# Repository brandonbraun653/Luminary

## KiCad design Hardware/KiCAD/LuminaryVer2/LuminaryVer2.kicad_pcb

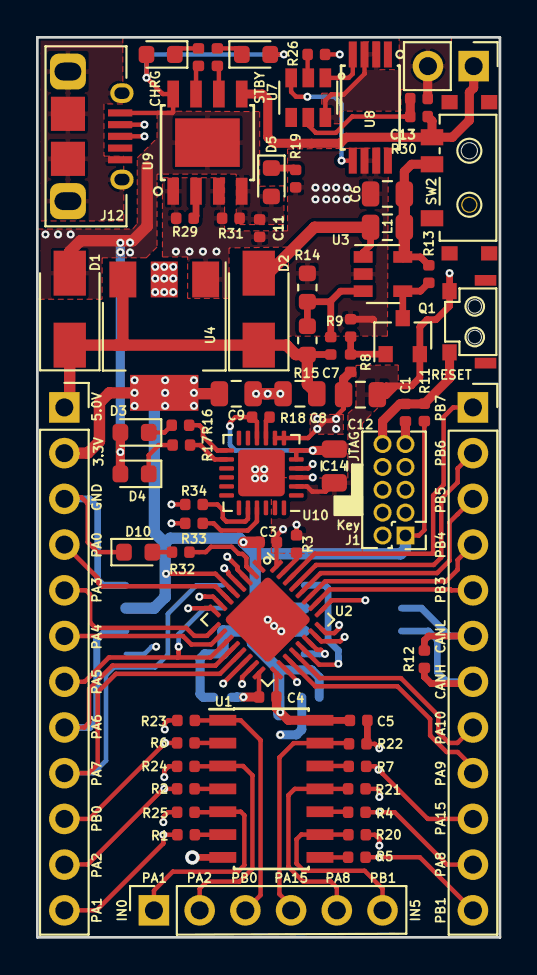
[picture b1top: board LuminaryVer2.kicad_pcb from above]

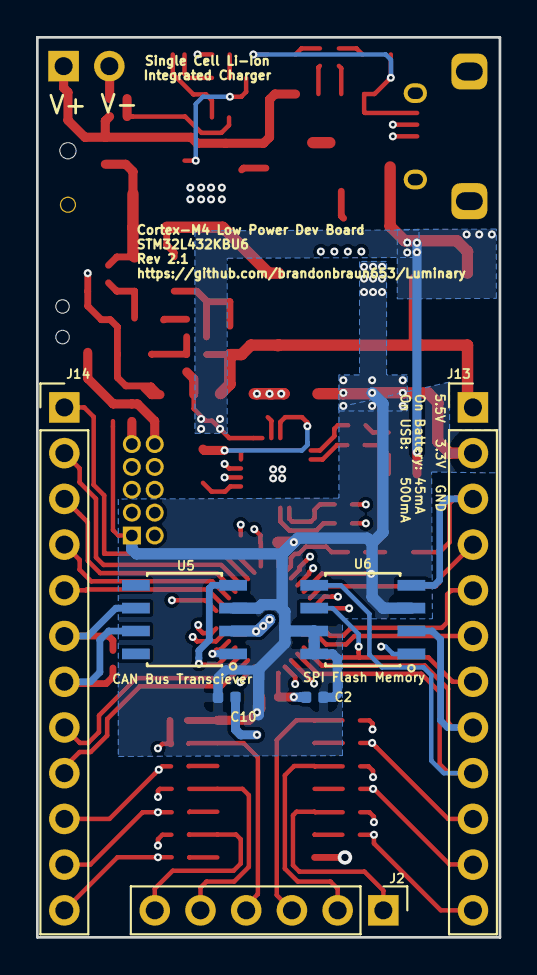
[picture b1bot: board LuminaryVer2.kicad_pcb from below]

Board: 4 copper layers, 25.7 x 50.0 mm, 75 parts (7 on the bottom side), 73 nets.

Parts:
C1, C2, C3, C4, C5, C10, C11, C13: 100nF; C_0402_1005Metric
C6, C8: 10uF; C_0805_2012Metric
C7: 3.3pF; C_0402_1005Metric
C9, C12, C14: 1uF; C_0805_2012Metric
D1, D2: SS14; D_SMA
D3, D4, D5, D9: BLED; D_0603_1608Metric
D8: RLED; D_0603_1608Metric
D10: GLED; D_0603_1608Metric
J1: JTAG; PinHeader_2x05_P1.27mm_Vertical
J2: GPIOInput; PinHeader_1x06_P2.54mm_Vertical
J10: ExtBattPwr; PinHeader_1x02_P2.54mm_Vertical
J12: USB_B_Micro; Amphenol-MicroB
J13: CN1; PinHeader_1x12_P2.54mm_Vertical
J14: CN2; PinHeader_1x12_P2.54mm_Vertical
L1: 3.3uH; L_0805_2012Metric
Q1: MMBT3904; SOT-23
R1, R2, R4, R5, R6, R7, R20, R21, R22, R23, R24, R25, R31: 47k; R_0402_1005Metric
R3, R9, R11, R13, R29, R32: 10k; R_0402_1005Metric
R8: 100; R_0402_1005Metric
R12, R30: 120; R_0402_1005Metric
R14: 200k; R_0603_1608Metric
R15: 620k; R_0603_1608Metric
R16, R17, R18, R19, R26, R27, R28, R33, R34: 1k; R_0402_1005Metric
SW1: SW_Push; LCSC_C255808_HYP_2x4x3.5mm_RightAngle
SW2: SW_BATT_DISCONNECT; LCSC_C136659_HRO_SPDT_6.7x2.6mm_ToggleSwitch
U1: 74HC14; SOIC-14_3.9x8.7mm_P1.27mm
U2: STM32L432KBUx; QFN-32-1EP_5x5mm_P0.5mm_EP3.45x3.45mm
U3: TPS61040; SOT-23-5
U4: AMS1117-3.3; SOT-223-3_TabPin2
U5: SN65HVD232; SOIC-8_3.9x4.9mm_P1.27mm
U6: AT25SF081-SSHD-X; SOIC-8_3.9x4.9mm_P1.27mm
U7: DW01+G; SOT-23-6
U8: FS8205A; TSSOP-8_4.4x3mm_P0.65mm
U9: TP4056; TP4056_SOP-8-PP
U10: CP2104; QFN-24-1EP_4x4mm_P0.5mm_EP2.6x2.6mm

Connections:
+3V3: C2.2, C3.1, C4.2, C5.2, C9.1, C10.2, J1.1, J13.2, R11.2, U1.14, U2.1, U2.5, U2.17, U4.2, U5.3, U6.3, U6.7, U6.8
+5V: C7.1, C8.2, D1.1, D2.1, J13.1, R15.1, U4.3
/Input Connectors/Batt_V+: J10.1, R30.1, SW2.1, U9.5
/Input Connectors/Batt_V-: C13.2, J10.2, U7.6, U8.2, U8.3
/Input Connectors/D+: J12.3, U10.3
/Input Connectors/D-: J12.2, U10.4
/Input Connectors/GPIO_INPUT_0: R1.1, U1.6
/Input Connectors/GPIO_INPUT_1: R2.2, U1.4
/Input Connectors/GPIO_INPUT_2: R6.2, U1.2
/Input Connectors/GPIO_INPUT_3: R7.2, U1.12
/Input Connectors/GPIO_INPUT_4: R4.2, U1.10
/Input Connectors/GPIO_INPUT_5: R5.2, U1.8
/Input Connectors/nRESET: C1.2, J1.10, R11.1, SW1.2, U2.4
/Output Connectors/CAN_1_HI: J14.7, R12.1, U5.7
/Output Connectors/CAN_1_LO: J14.6, R12.2, U5.6
/Output Connectors/I2C_1_SCL: J14.2, U2.29
/Output Connectors/I2C_1_SDA: J14.1, U2.30
/Output Connectors/RS232_1_RX: J14.8, R33.2, U2.20
/Output Connectors/RS232_1_TX: J14.9, R34.2, U2.19
/Output Connectors/SPI_1_MISO: J13.8, U2.12, U6.2
/Output Connectors/SPI_1_MOSI: J13.9, U2.13, U6.5
/Output Connectors/SPI_1_SCK: J13.7, U2.11, U6.6
/Output Connectors/SPI_2_MISO: J14.4, U2.27
/Output Connectors/SPI_2_MOSI: J14.3, U2.28
/Output Connectors/SPI_2_SCK: J14.5, U2.26
/Power Supply/Ext_In+: C11.1, C12.2, D1.2, D3.2, D4.2, D5.2, D8.2, D9.2, J12.1, R8.2, R31.2, U9.4, U9.8, U9.9, U10.7, U10.8
/Processor/ADC_0: J13.4, U2.6
/Processor/ADC_1: J13.5, U2.9
/Processor/ADC_2: J13.6, U2.10
/Processor/CAN_1_RX: U2.21, U5.4
/Processor/CAN_1_TX: U2.22, U5.1
/Processor/GPIO_0: J13.12, R1.2, U2.7
/Processor/GPIO_1: J13.11, R2.1, U2.8
/Processor/GPIO_2: J13.10, R6.1, U2.14
/Processor/GPIO_3: J14.10, R7.1, U2.25
/Processor/GPIO_4: J14.11, R4.1, U2.18
/Processor/GPIO_5: J14.12, R5.1, U2.15
/Processor/SWCLK: J1.4, U2.24
/Processor/SWDIO: J1.2, U2.23
FlashCS: U2.3, U6.1
GND: C1.1, C2.1, C3.2, C4.1, C5.1, C6.1, C8.1, C9.2, C10.1, C11.2, C12.1, C14.2, D10.1, J1.3, J1.5, J1.9, J12.5, J12.6, J13.3, Q1.2, R3.2, R9.1, R14.1, R19.1, R20.1, R21.1, R22.1, R23.1, R24.1, R25.1, R26.2, R29.2, R31.1, SW1.1, U1.7, U2.16, U2.32, U2.33, U3.2, U4.1, U5.2, U6.4, U8.6, U8.7, U9.1, U9.3, U10.2, U10.25
unnamed: C6.2, L1.1, R13.2, SW2.2, U3.5
unnamed: C7.2, R14.2, R15.2, U3.3
unnamed: C13.1, R30.2, U7.5
unnamed: C14.1, R18.2, U10.5, U10.6, U10.10
unnamed: D2.2, L1.2, U3.1
unnamed: D3.1, R16.2
unnamed: D4.1, R17.2
unnamed: D5.1, R19.2
unnamed: D8.1, R27.2
unnamed: D9.1, R28.2
unnamed: D10.2, R32.1
unnamed: J2.1, R25.2, U1.5
unnamed: J2.2, R24.2, U1.3
unnamed: J2.3, R23.2, U1.1
unnamed: J2.4, R22.2, U1.13
unnamed: J2.5, R21.2, U1.11
unnamed: J2.6, R20.2, U1.9
unnamed: Q1.1, R8.1, R9.2
unnamed: Q1.3, R13.1, U3.4
unnamed: R3.1, U2.31
unnamed: R16.1, U10.13
unnamed: R17.1, U10.14
unnamed: R18.1, U10.9
unnamed: R26.1, U7.2
unnamed: R27.1, U9.7
unnamed: R28.1, U9.6
unnamed: R29.1, U9.2
unnamed: R33.1, U10.21
unnamed: R34.1, U10.20
unnamed: U7.1, U8.4
unnamed: U7.3, U8.5
StatusLED: R32.2, U2.2

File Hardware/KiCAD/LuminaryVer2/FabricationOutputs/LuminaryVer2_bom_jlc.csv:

"Comment","Designator","Footprint","LCSC Part #"
"100nF","C5,C13,C11,C3,C4,C1,C2,C10","C_0402_1005Metric","C1525"
"10uF","C6,C8","C_0805_2012Metric","C15850"
"3.3pF","C7","C_0402_1005Metric","C1565"
"1uF","C9,C14,C12","C_0805_2012Metric","C28323"
"SS14","D1,D2","D_SMA","C2480"
"RLED","D8","D_0603_1608Metric","C2286"
"BLED","D9,D5,D4,D3","D_0603_1608Metric","C72041"
"GLED","D10","D_0603_1608Metric","C72043"
"3.3uH","L1","L_0805_2012Metric","C51725"
"MMBT3904","Q1","SOT-23","C20526"
"100","R8","R_0402_1005Metric","C25076"
"10k","R9,R29,R13,R3,R11,R32","R_0402_1005Metric","C25744"
"200k","R14","R_0603_1608Metric","C25811"
"620k","R15","R_0603_1608Metric","C23219"
"47k","R25,R23,R21,R22,R24,R20,R31,R1,R2,R6,R7,R4,R5","R_0402_1005Metric","C25792"
"1k","R27,R28,R26,R19,R16,R17,R18,R33,R34","R_0402_1005Metric","C11702"
"120","R30,R12","R_0402_1005Metric","C25079"
"SW_Push","SW1","LCSC_C255808_HYP_2x4x3.5mm_RightAngle","C255808"
"SW_BATT_DISCONNECT","SW2","LCSC_C136659_HRO_SPDT_6.7x2.6mm_ToggleSwitch","C136659"
"74HC14","U1","SOIC-14_3.9x8.7mm_P1.27mm","C5605"
"STM32L432KBUx","U2","QFN-32-1EP_5x5mm_P0.5mm_EP3.45x3.45mm","C94784"
"TPS61040","U3","SOT-23-5","C7722"
"AMS1117-3.3","U4","SOT-223-3_TabPin2","C6186"
"SN65HVD232","U5","SOIC-8_3.9x4.9mm_P1.27mm","C30530"
"AT25SF081-SSHD-X","U6","SOIC-8_3.9x4.9mm_P1.27mm","C169368"
"DW01+G","U7","SOT-23-6","C14213"
"FS8205A","U8","TSSOP-8_4.4x3mm_P0.65mm","C16052"
"TP4056","U9","TP4056_SOP-8-PP","C16581"
"CP2104","U10","QFN-24-1EP_4x4mm_P0.5mm_EP2.6x2.6mm","C47742"

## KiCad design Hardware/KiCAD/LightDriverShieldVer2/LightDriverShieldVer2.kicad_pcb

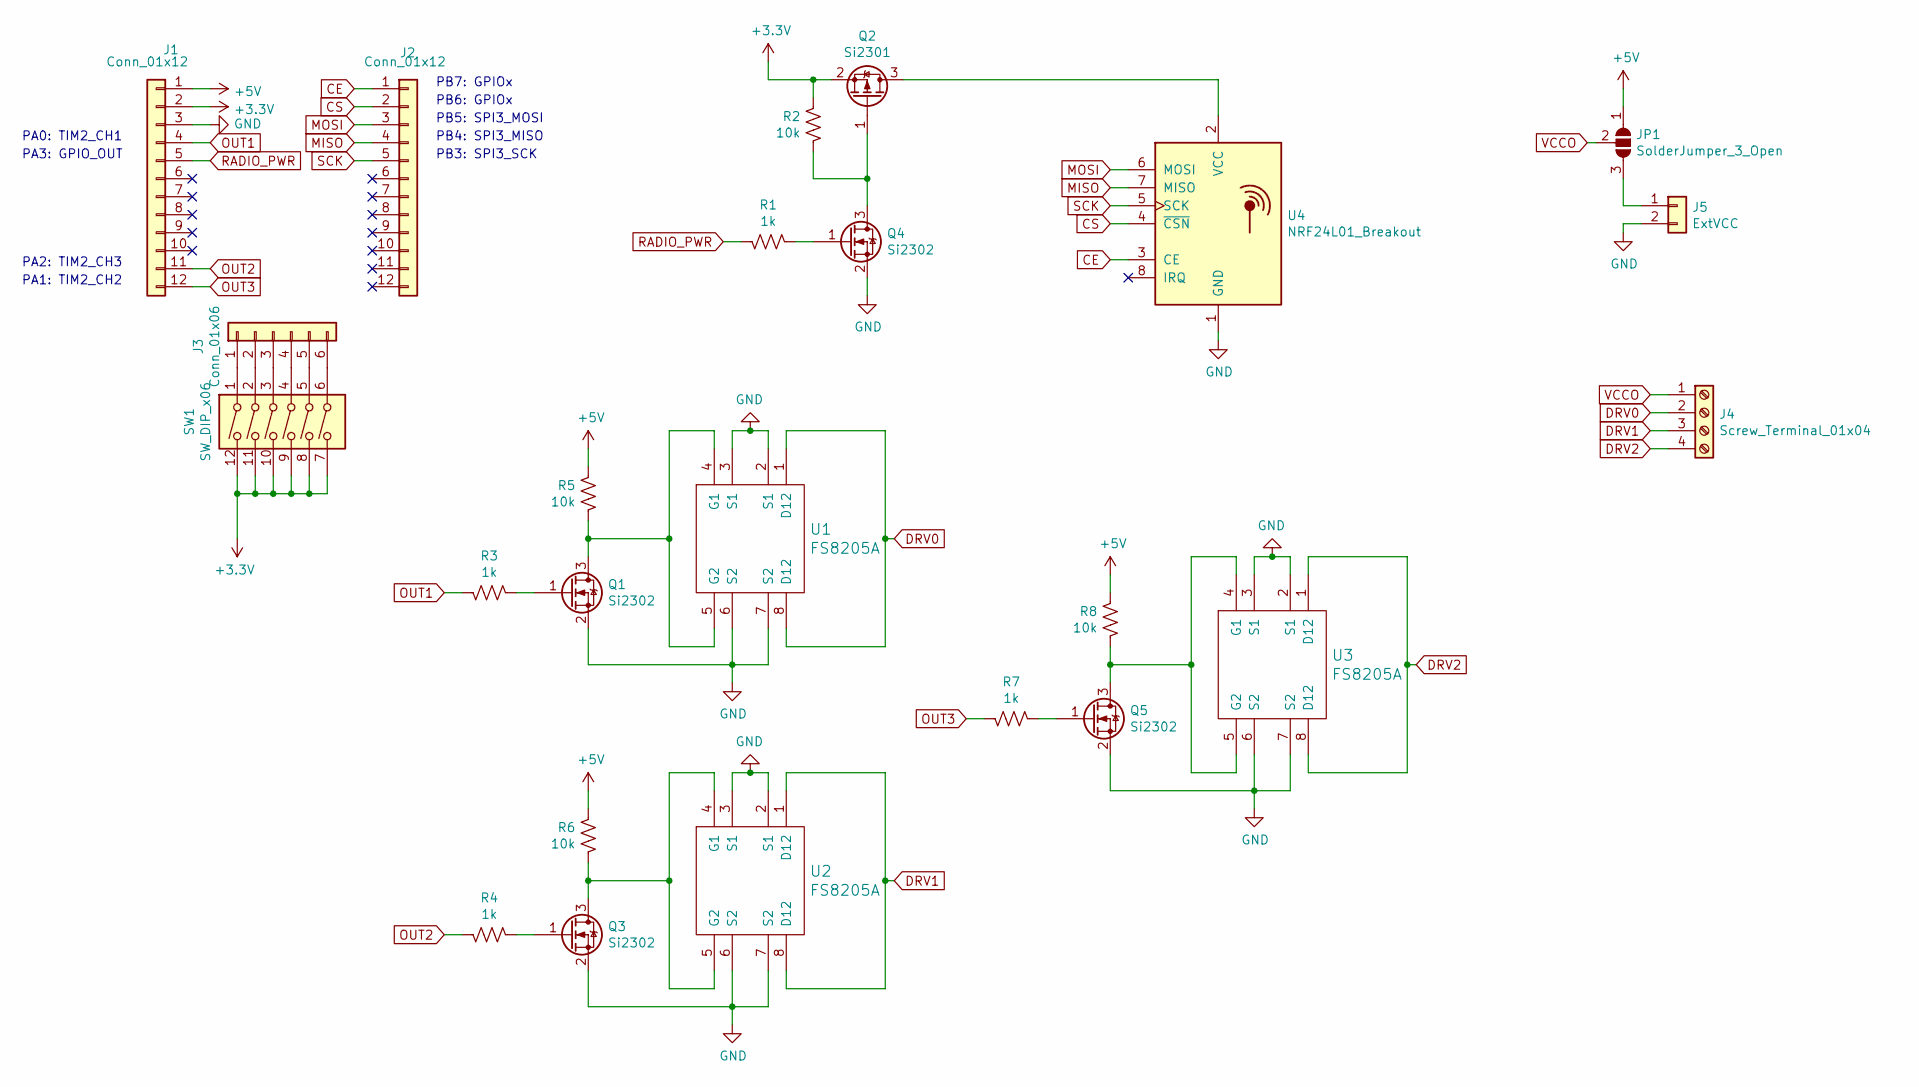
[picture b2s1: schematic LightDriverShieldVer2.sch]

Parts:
J1, J2: Conn_01x12; PinSocket_1x12_P2.54mm_Vertical
J3: Conn_01x06; PinSocket_1x06_P2.54mm_Vertical
J4: Screw_Terminal_01x04; TerminalBlock_TE_282834-4_1x04_P2.54mm_Horizontal
J5: ExtVCC; PinHeader_1x02_P2.54mm_Vertical
JP1: SolderJumper_3_Open; SolderJumper-3_P2.0mm_Open_TrianglePad1.0x1.5mm_NumberLabels
Q1, Q3, Q4, Q5: Si2302; SOT-23; LCSC C181087
Q2: Si2301; SOT-23; LCSC C10487
R1, R3, R4, R7: 1k; R_0402_1005Metric
R2, R5, R6, R8: 10k; R_0402_1005Metric
SW1: SW_DIP_x06; SW_DIP_SPSTx06_Slide_6.7x16.8mm_W7.62mm_P2.54mm_LowProfile
U1, U2, U3: FS8205A; TSSOP-8_4.4x3mm_P0.65mm; LCSC C16052
U4: NRF24L01_Breakout; nRF24L01_Breakout

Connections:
+3V3: J1.2, Q2.2 (S), R2.2, SW1.7, SW1.8, SW1.9, SW1.10, SW1.11, SW1.12
+5V: J1.1, JP1.1 (A), R5.2, R6.2, R8.2
CE: J2.1, U4.3 (CE)
CS: J2.2, U4.4 (~CSN)
DRV0: J4.2, U1.1 (D12), U1.8 (D12)
DRV1: J4.3, U2.1 (D12), U2.8 (D12)
DRV2: J4.4, U3.1 (D12), U3.8 (D12)
GND: J1.3, J5.2, Q1.2 (S), Q3.2 (S), Q4.2 (S), Q5.2 (S), U1.2 (S1), U1.3 (S1), U1.6 (S2), U1.7 (S2), U2.2 (S1), U2.3 (S1), U2.6 (S2), U2.7 (S2), U3.2 (S1), U3.3 (S1), U3.6 (S2), U3.7 (S2), U4.1 (GND)
MISO: J2.4, U4.7 (MISO)
MOSI: J2.3, U4.6 (MOSI)
unnamed: J3.1, SW1.1
unnamed: J3.2, SW1.2
unnamed: J3.3, SW1.3
unnamed: J3.4, SW1.4
unnamed: J3.5, SW1.5
unnamed: J3.6, SW1.6
unnamed: J5.1, JP1.3 (B)
unnamed: Q1.1 (G), R3.2
unnamed: Q1.3 (D), R5.1, U1.4 (G1), U1.5 (G2)
unnamed: Q2.1 (G), Q4.3 (D), R2.1
unnamed: Q2.3 (D), U4.2 (VCC)
unnamed: Q3.1 (G), R4.2
unnamed: Q3.3 (D), R6.1, U2.4 (G1), U2.5 (G2)
unnamed: Q4.1 (G), R1.2
unnamed: Q5.1 (G), R7.2
unnamed: Q5.3 (D), R8.1, U3.4 (G1), U3.5 (G2)
OUT1: J1.4, R3.1
OUT2: J1.11, R4.1
OUT3: J1.12, R7.1
RADIO_PWR: J1.5, R1.1
SCK: J2.5, U4.5 (SCK)
VCCO: J4.1, JP1.2 (C)

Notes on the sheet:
PA0: TIM2_CH1
PA1: TIM2_CH2
PA2: TIM2_CH3
PB7: GPIOx
PB6: GPIOx
PB3: SPI3_SCK
PB4: SPI3_MISO
PB5: SPI3_MOSI
PA3: GPIO_OUT

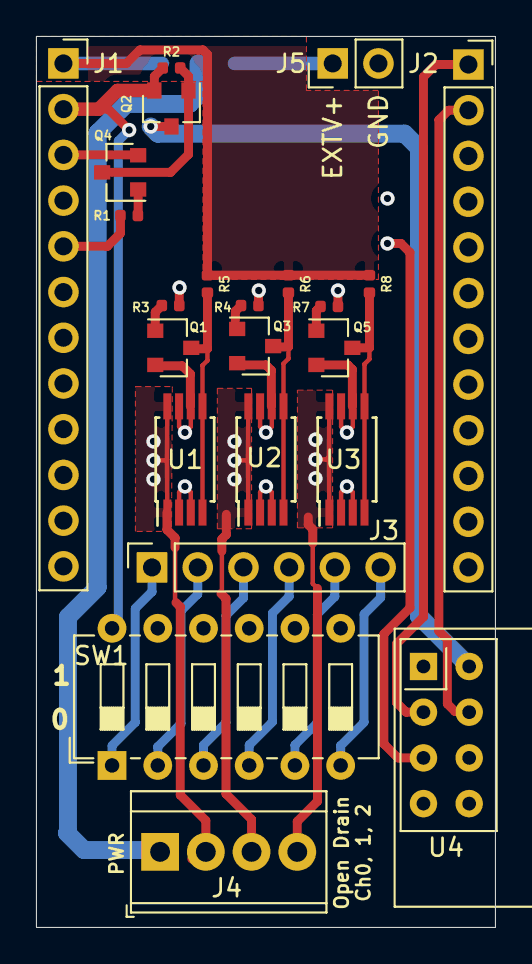
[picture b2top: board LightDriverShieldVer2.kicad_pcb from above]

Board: 4 copper layers, 25.5 x 49.5 mm, 24 parts (1 on the bottom side), 32 nets.

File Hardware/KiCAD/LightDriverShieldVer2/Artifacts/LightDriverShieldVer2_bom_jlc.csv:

"Comment","Designator","Footprint","LCSC Part #"
"Conn_01x12","J1,J2","PinSocket_1x12_P2.54mm_Vertical","C225509"
"Conn_01x06","J3","PinSocket_1x06_P2.54mm_Vertical","C40877"
"Si2302","Q1,Q3,Q5,Q4","SOT-23","C181087"
"Si2301","Q2","SOT-23","C10487"
"1k","R1,R3,R4,R7","R_0402_1005Metric","C11702"
"10k","R2,R5,R6,R8","R_0402_1005Metric","C25744"
"SW_DIP_x06","SW1","SW_DIP_SPSTx06_Slide_6.7x16.8mm_W7.62mm_P2.54mm_LowProfile","C319058"
"FS8205A","U1,U2,U3","TSSOP-8_4.4x3mm_P0.65mm","C16052"

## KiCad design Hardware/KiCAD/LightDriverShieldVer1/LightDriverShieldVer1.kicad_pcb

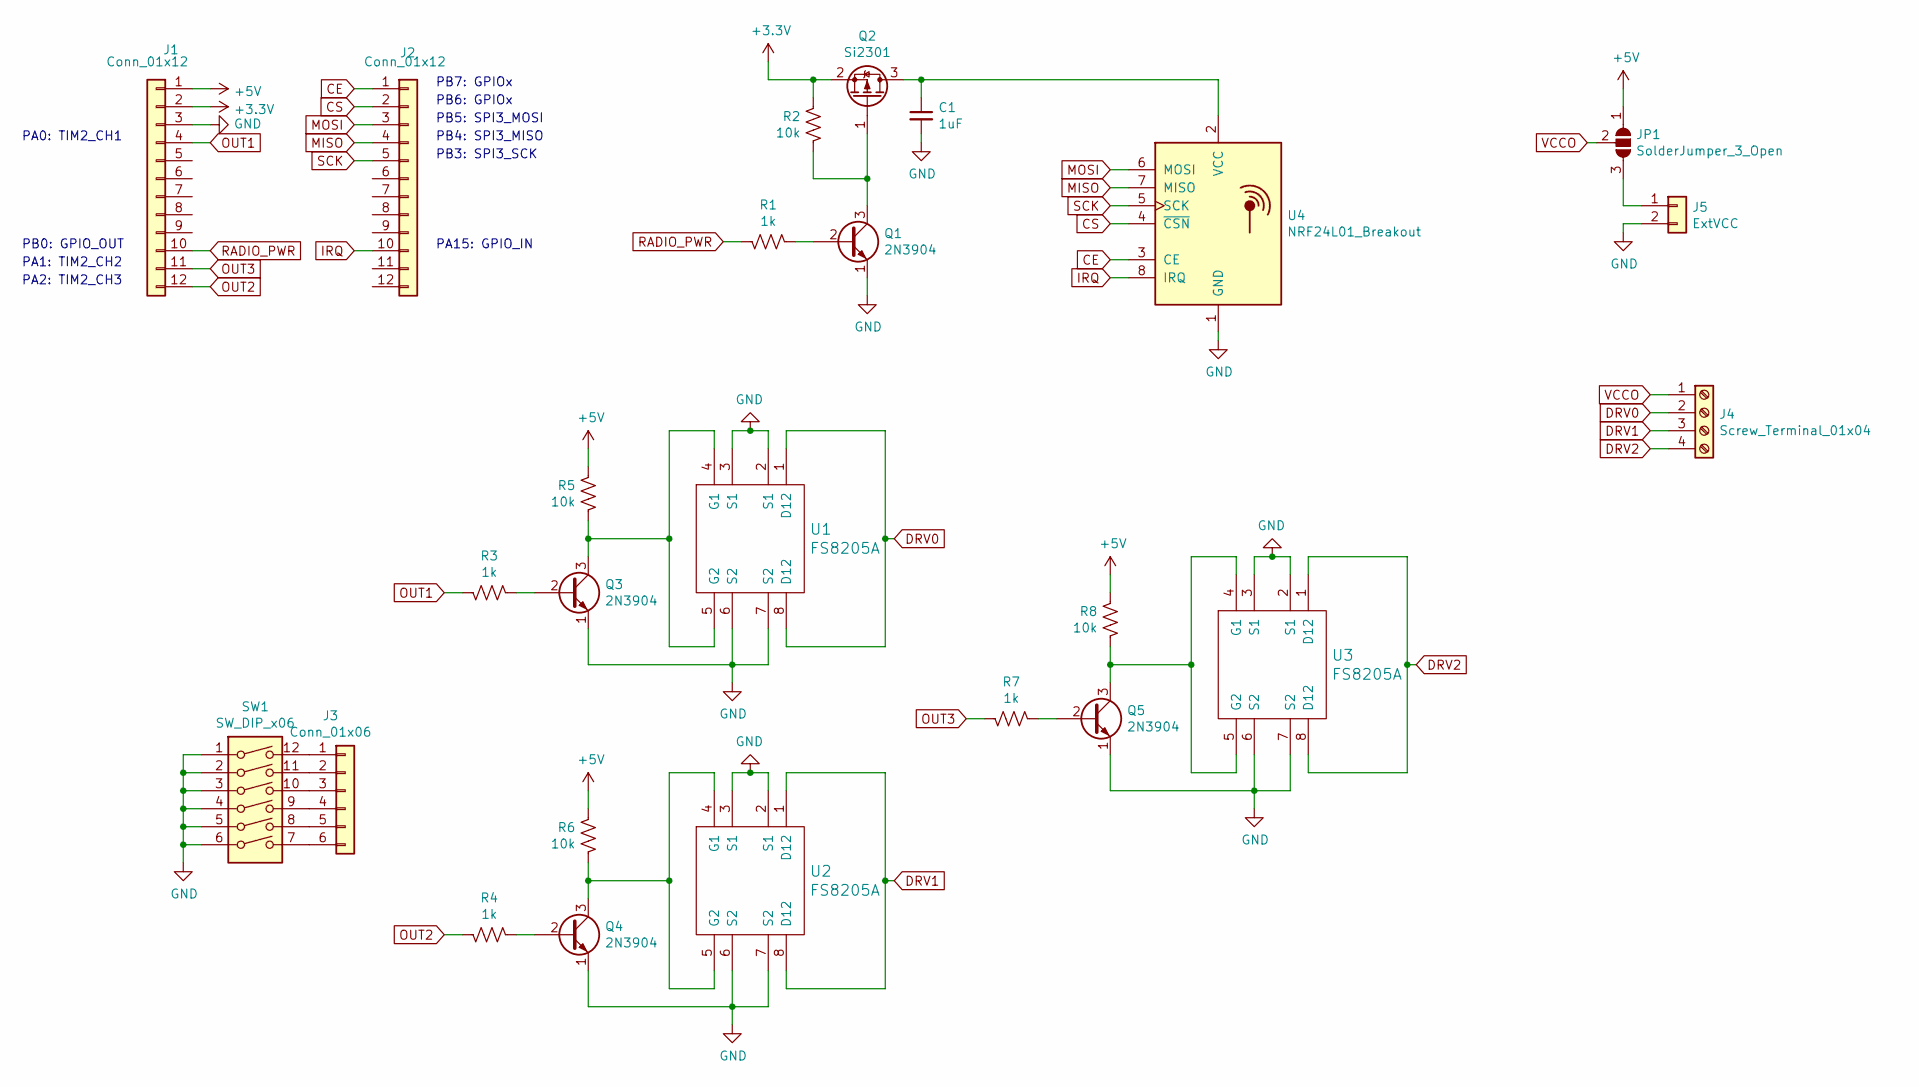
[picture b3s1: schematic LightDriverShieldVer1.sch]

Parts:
C1: 1uF; C_0402_1005Metric; LCSC C52923
J1, J2: Conn_01x12; PinSocket_1x12_P2.54mm_Vertical
J3: Conn_01x06; PinSocket_1x06_P2.54mm_Vertical
J4: Screw_Terminal_01x04; TerminalBlock_TE_282834-4_1x04_P2.54mm_Horizontal
J5: ExtVCC; PinHeader_1x02_P2.54mm_Vertical
JP1: SolderJumper_3_Open; SolderJumper-3_P2.0mm_Open_TrianglePad1.0x1.5mm_NumberLabels
Q1, Q3, Q4, Q5: 2N3904; SOT-23; LCSC C18536
Q2: Si2301; SOT-23; LCSC C10487
R1, R3, R4, R7: 1k; R_0402_1005Metric
R2, R5, R6, R8: 10k; R_0402_1005Metric
SW1: SW_DIP_x06; SW_DIP_SPSTx06_Slide_6.7x16.8mm_W7.62mm_P2.54mm_LowProfile
U1, U2, U3: FS8205A; TSSOP-8_4.4x3mm_P0.65mm; LCSC C16052
U4: NRF24L01_Breakout; nRF24L01_Breakout

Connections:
+3V3: J1.2, Q2.2 (S), R2.2
+5V: J1.1, JP1.1 (A), R5.2, R6.2, R8.2
CE: J2.1, U4.3 (CE)
CS: J2.2, U4.4 (~CSN)
DRV0: J4.2, U1.1 (D12), U1.8 (D12); also elsewhere on the board
DRV1: J4.3, U2.1 (D12), U2.8 (D12); also elsewhere on the board
DRV2: J4.4, U3.1 (D12), U3.8 (D12); also elsewhere on the board
GND: C1.2, J1.3, J5.2, Q1.1 (E), Q3.1 (E), Q4.1 (E), Q5.1 (E), SW1.1, SW1.2, SW1.3, SW1.4, SW1.5, SW1.6, U1.2 (S1), U1.3 (S1), U1.6 (S2), U1.7 (S2), U2.2 (S1), U2.3 (S1), U2.6 (S2), U2.7 (S2), U3.2 (S1), U3.3 (S1), U3.6 (S2), U3.7 (S2), U4.1 (GND)
IRQ: J2.10, U4.8 (IRQ)
MISO: J2.4, U4.7 (MISO)
MOSI: J2.3, U4.6 (MOSI)
unnamed: C1.1, Q2.3 (D), U4.2 (VCC)
unnamed: J3.1, SW1.12
unnamed: J3.2, SW1.11
unnamed: J3.3, SW1.10
unnamed: J3.4, SW1.9
unnamed: J3.5, SW1.8
unnamed: J3.6, SW1.7
unnamed: J5.1, JP1.3 (B)
unnamed: Q1.2 (B), R1.2
unnamed: Q1.3 (C), Q2.1 (G), R2.1
unnamed: Q3.2 (B), R3.2
unnamed: Q3.3 (C), R5.1, U1.4 (G1), U1.5 (G2)
unnamed: Q4.2 (B), R4.2
unnamed: Q4.3 (C), R6.1, U2.4 (G1), U2.5 (G2)
unnamed: Q5.2 (B), R7.2
unnamed: Q5.3 (C), R8.1, U3.4 (G1), U3.5 (G2)
OUT1: J1.4, R3.1
OUT2: J1.12, R4.1
OUT3: J1.11, R7.1
RADIO_PWR: J1.10, R1.1
SCK: J2.5, U4.5 (SCK)
VCCO: J4.1, JP1.2 (C)

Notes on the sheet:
PA0: TIM2_CH1
PA1: TIM2_CH2
PA2: TIM2_CH3
PB0: GPIO_OUT
PB7: GPIOx
PB6: GPIOx
PB3: SPI3_SCK
PB4: SPI3_MISO
PB5: SPI3_MOSI
PA15: GPIO_IN

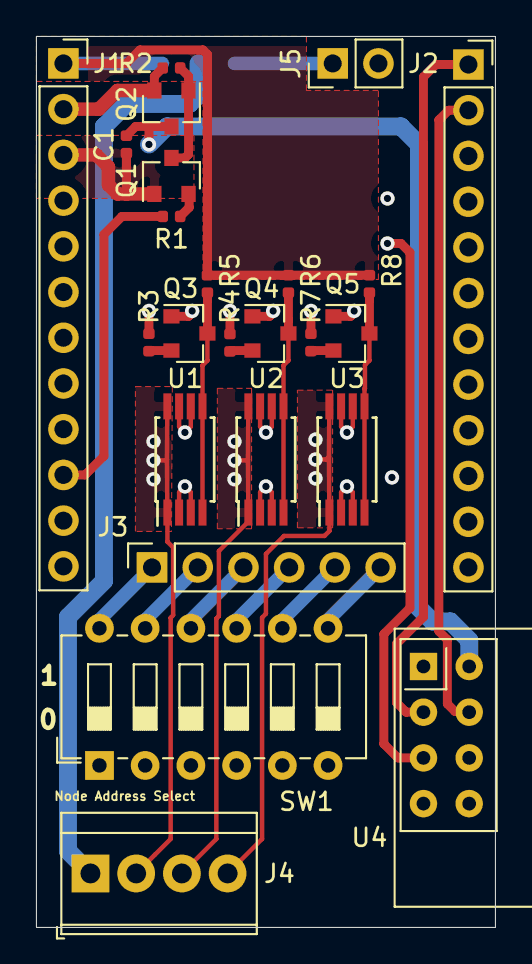
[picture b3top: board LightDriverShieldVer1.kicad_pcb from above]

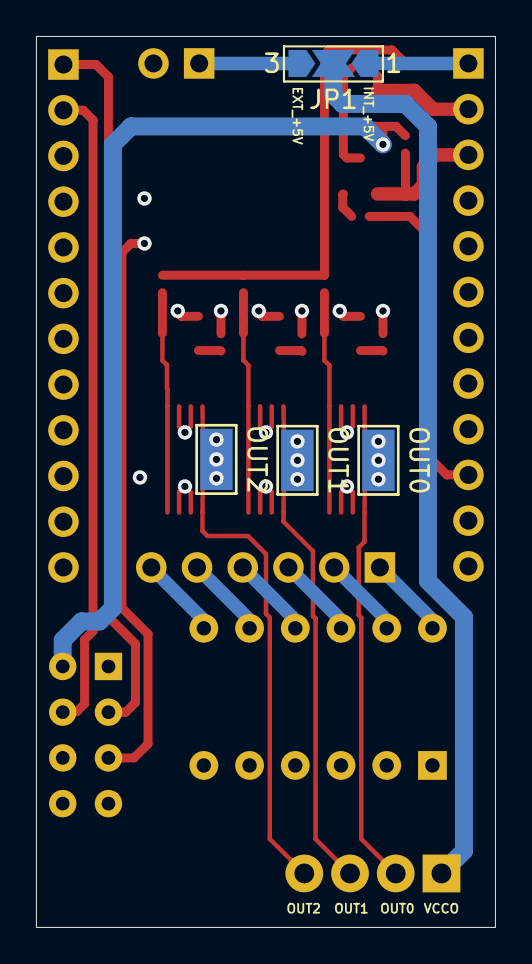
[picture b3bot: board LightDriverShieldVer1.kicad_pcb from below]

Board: 4 copper layers, 25.5 x 49.5 mm, 28 parts (4 on the bottom side), 33 nets.

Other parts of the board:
OUT0, OUT1, OUT2: TestPoint_Keystone_5015_Micro-Minature

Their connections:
DRV0: OUT0.1; also elsewhere on the board
DRV1: OUT1.1; also elsewhere on the board
DRV2: OUT2.1; also elsewhere on the board

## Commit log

2020-02-07 Added KiCAD project for PCB revision 1.
2020-02-08 Removed GPIO output driver to increase versatility as IO. Added passive over-current/voltage protection.
2020-03-08 Added the directory structure for the software.
2020-03-23 Added empty BOM for LCSC
2020-03-23 Added STM32Cube planning project.
2020-03-30 Added core submodules
2020-05-08 Added PMIC and charging circuitry. Minor refresh of existing components. Added KiCAD component lib.
2020-05-08 Added missing gitmodules entry for kicad parts repo
2020-05-09 Routed entire power section
2020-05-13 Added majority of the logic level circuitry. Almost done routing connections.
2020-05-14 Finalized for version 1 production.
2020-05-18 Added embedded build project for Luminary. Created driver for the status LED. Submodule updates.
2020-05-18 Added power selection driver. Updated RF24Node and Thor drivers to try and figure out why SPI isn't writing.
2020-05-18 Update vscode properties to help find header files easier.
2020-05-21 Added logging. Started working on getting the networking driver up and running.
2020-05-21 Fixed SPI communication issue by pulling up submodules.
2020-05-21 Added empty project for led driver shield
2020-05-23 Pull up submodules. Added project side observable initialization.
2020-05-23 Added missing files from last commit
2020-05-23 Pull up submodules to get Serial driver support. Added basic thread entry point for the RPC server.
2020-05-25 Pull up submodules. Started adding scaffolding for serial command parsing.
2020-05-25 Added command parser functionality.
2020-05-29 Pull up submodules. Implement a good chunk of the build system. Address a few build errors.
2020-06-04 Working on embedded target. Pull up submodules.
2020-06-07 Added processing for auto-reconnection to the network. Started on V2 of luminary hardware. Pull up submodules.
2020-06-08 Updated version 2 hardware schematics.
2020-06-08 Add silk screen overlay to pins. Redo GPIO input to use LCSC basic part.
2020-06-10 Laid out the power supply updates.
2020-06-10 Routed most of the signal layer.
2020-06-10 Version two nets fully routed.
2020-06-10 Update some of the ground pours.
2020-06-11 Luminary V2 complete & sent off for manufacturing
2020-06-13 Added initial schematic for Luminary daughter board.
2020-06-14 Routed the shield for version 1
2020-06-15 Shield version 1 ordered.
2020-06-18 Generated interactive BOM for the lightdrivershield
2020-06-26 Document a hardware bug with the power supply in version two of Luminary.
2020-06-27 Documented hardware bugs in LightDriverShieldVer1
2020-06-30 Pull up submodules. Added PWM output driver.
2020-07-01 Rev the LightDriver board to version 2.
2020-07-04 Hardware drivers reached stable operation. Transitioning to application layer development.
2020-07-05 Prototype animations working on the output drivers.
2020-07-06 GCC toolchain update in VGDB project. Implemented independent channel animations for flame/sinewave.
2020-07-09 Added Test project for exercising Luminary drivers.
2020-07-13 Added support for multi-node message passing/handling. Seems to work ok.
2020-07-13 Update radio driver to pull in bug fix
2020-07-17 Stash for partial implementation.
2020-07-19 Fully implemented fix
2020-07-19 Integrated RF24 driver updates for improved network communication.
2020-07-21 Pull up RF24 driver for ShockBurst protocol implementation.
2020-07-23 Swapped MMBT3904 BJTs to SI2302 NMOS. Fixes bug where the B-E junction forces the GPIO pin controlling ON/OFF state to be clamped at ~0.6v.
2020-07-23 Finalized hardware 2.3
2020-07-24 Add a few new routines.
2020-07-27 Updated the animations to be closer to their final state.
2020-08-02 VGDB Toolchain updates.
2020-08-02 Update LED handling to display status codes. Improve network connection algorithm.
2020-08-05 Save for move to laptop
2020-08-06 Improve the radio driver.
2020-08-06 Candidate software version 1.1.0
2020-08-06 Candidate build 1.1.1. Extended mode changes to 5 minutes and mapped the network addresses.
